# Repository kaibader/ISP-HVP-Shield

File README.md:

# ISP-HVP-Shield

Arduino ISP and HVSP/HVPP Shield for ATtiny Microcontoller

## Preface

**This repository is discontinued and only provided for others to further work
with its content.**

Eagle CAD version 7 was used to create the schematic and board files. The latest
version I've tested was Eagle CAD v7.7. I do not support the price and product
policy of Autodesk and therefore have moved from Eagle CAD to the free and open
source KiCad. I can only recommend you to do the same.

## Version 1.0

This is the original version of the Arduino ISP shield which not only has been
successfully tested but also copied/created by various other users.

**If you are unsure which version to use for further experiments stick to this
one.**

## Version 1.1

This was a slightly improved version of the original ATtiny ISP Shield.
This version was *never produced and never tested* as real hardware.

## Version 2.0

This was an experimental version which not only should allow the programming
of ATtiny microcontollers but also erase their fuses (via high voltage
programming).

The TopoR autorouter was used to route the v2.0 board which then was used to
generate the Gerber files. I've added an ripped-up version of the board for
compatibility reasons.

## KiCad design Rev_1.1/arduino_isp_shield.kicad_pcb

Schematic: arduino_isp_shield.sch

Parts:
C1, C2: 0.1uF; C_Disc_D3.8mm_W2.6mm_P2.50mm
C4: 10uF; CP_Radial_D5.0mm_P2.50mm
J1: ISP; PinHeader_2x03_P2.54mm_Vertical
J2: Conn_01x08; PinHeader_1x08_P2.54mm_Vertical
J3: Conn_01x10; PinHeader_1x10_P2.54mm_Vertical
U1: ATTINY13/15/25/45/85; DIP-8_W7.62mm
U2: ATTINY24/44/84; DIP-14_W7.62mm
U3: ATTINY2313/4313; DIP-20_W7.62mm

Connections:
+5V: C1.1, C2.1, J1.2, J2.5, U1.8 (VCC), U2.1 (VCC), U3.20
/MISO: J1.1, J3.6, U1.6 (PB1(MISO/DO/AIN1/OC0B/OC1A/PCINT1)), U2.8 ((PCINT5/DO/MISO/OC1B/ADC5)PA5), U3.18
/MOSI: J1.4, J3.7, U1.5 (PB0(MOSI/DI/SDA/AIN0/OC0A/OC1A/AREF/PCI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), U2.7 ((PCINT6/SDA/DI/MOSI/OC1A/ADC6)PA6), U3.17
/SCK: J1.3, J3.5, U1.7 (PB2(SCK/USCK/SCL/T0/INT0/ADC1/PCINT2)), U2.9 ((PCINT4/USCK/SCL/T1/ADC4)PA4), U3.19
/~RESET: J1.5, J3.8, U1.1 (PB5(~RESET~/dW/ADC0/PCINT5)), U2.4 ((PCINT11/dW/~RESET~)PB3), U3.1
GND: C1.2, C2.2, C4.2, J1.6, J2.6, J2.7, J3.4, U1.4 (GND), U2.14 (GND), U3.10
unnamed: C4.1, J2.3

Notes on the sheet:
Decoupling Capacitors (optional)
Optional/External ISP

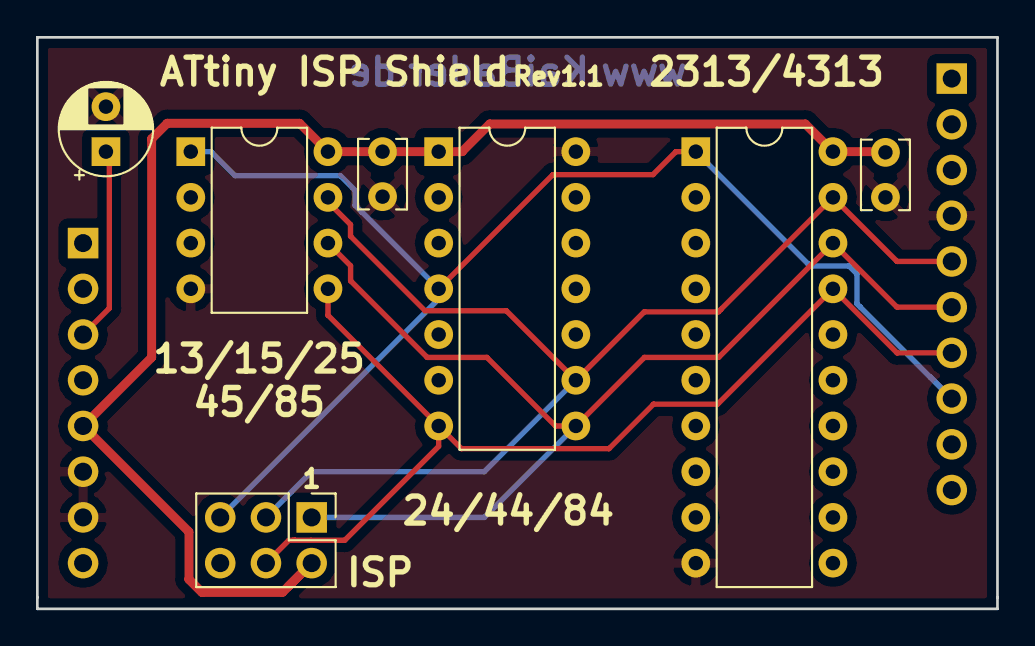
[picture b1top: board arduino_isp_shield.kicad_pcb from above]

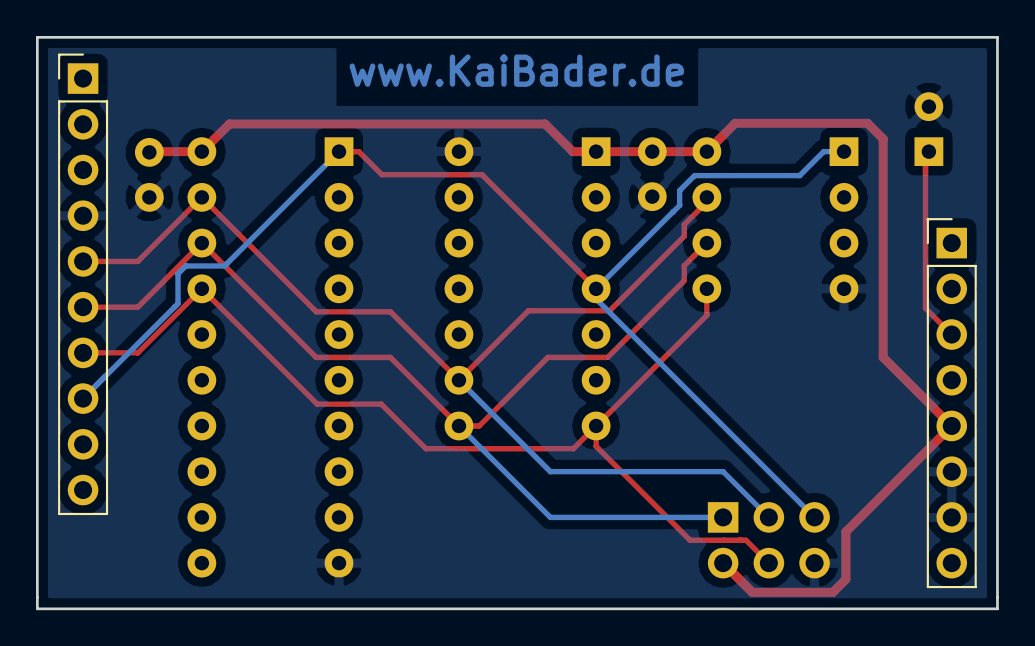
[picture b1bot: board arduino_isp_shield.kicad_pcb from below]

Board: 2 copper layers, 53.3 x 31.8 mm, 9 parts (2 on the bottom side), 7 nets.

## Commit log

2013-10-22 Initial commit (ignore list). This is a repository of my Eagle CAD files.
2013-10-22 Added new files. May need to be cleaned up later...
2015-03-19 New design. Started to add HVSP/HVPP features.
2015-03-20 Added test board 'optimized' with topor.
2015-03-21 Added Gerber files.
2015-03-21 Sent Gerber files to fab house...
2015-03-26 Some clean-up.
2015-04-19 A little bit of housecleaning...
2015-04-25 More cleaning...
2017-04-13 Fixed the forward<->backward compatibility.
    - Ripped up the board file to fix the schematic board compatibility.
    - Moved the TopoR (auto)routed board to a different location.
2017-04-13 Created a README.md comment
2018-02-13 Updated the Ignore List
2018-02-14 New Revision 1.1 Board designed with KiCad
    This board is identical to Revision 1.0 besides two instead of one
    decoupling capacitor and a new layout.
2018-02-15 Minor adaptions: improved the alignment of some traces.
2018-02-15 Minor fix due to DRC warning
2018-02-15 Renamed the Gerber files
2018-02-15 Minor Silk Screen Fix
2018-06-12 Renamed 'Revision_*' into 'Version_*'... avoids confusion.
